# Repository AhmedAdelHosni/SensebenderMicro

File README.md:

# Sensebender Micro

UPDATE: The board was tested during month September 2017 and it works fine as a BETA testing.

This is a micro sensor module for Mysensors project: http://www.mysensors.org

Designed to run on 2 x AA(A) batteries, depending on how often one would
like to replace the batteries. 

This branch replaces the 0402 passive components to 0603 package size.

The sensor includes the following peripherals
- Jedec compatible eeprom/flash footprint
- ATSHA204A for authentication

This branch removed the following
- Si7021 Temperature / Humidity sensor (Connected to I2C bus)
- LED

The following pins are available on headers:

- Powersupply (1.8 -> 3.5V)
- SDA / SCL (I2C bus)
- A0 / A1
- D3 / D4 / D5 / D6 / D7
- 6 pin ISP port
- 8 pin standard NRF24L01+ connector layout
- FTDI header for serial

*Please note*

MAXIMUM allowed supply voltage is 3.5V, anything above this WILL fry both
radio and NRF24 radio module. There is NO voltage regulator on board (To keep
supply current down to a minimum)

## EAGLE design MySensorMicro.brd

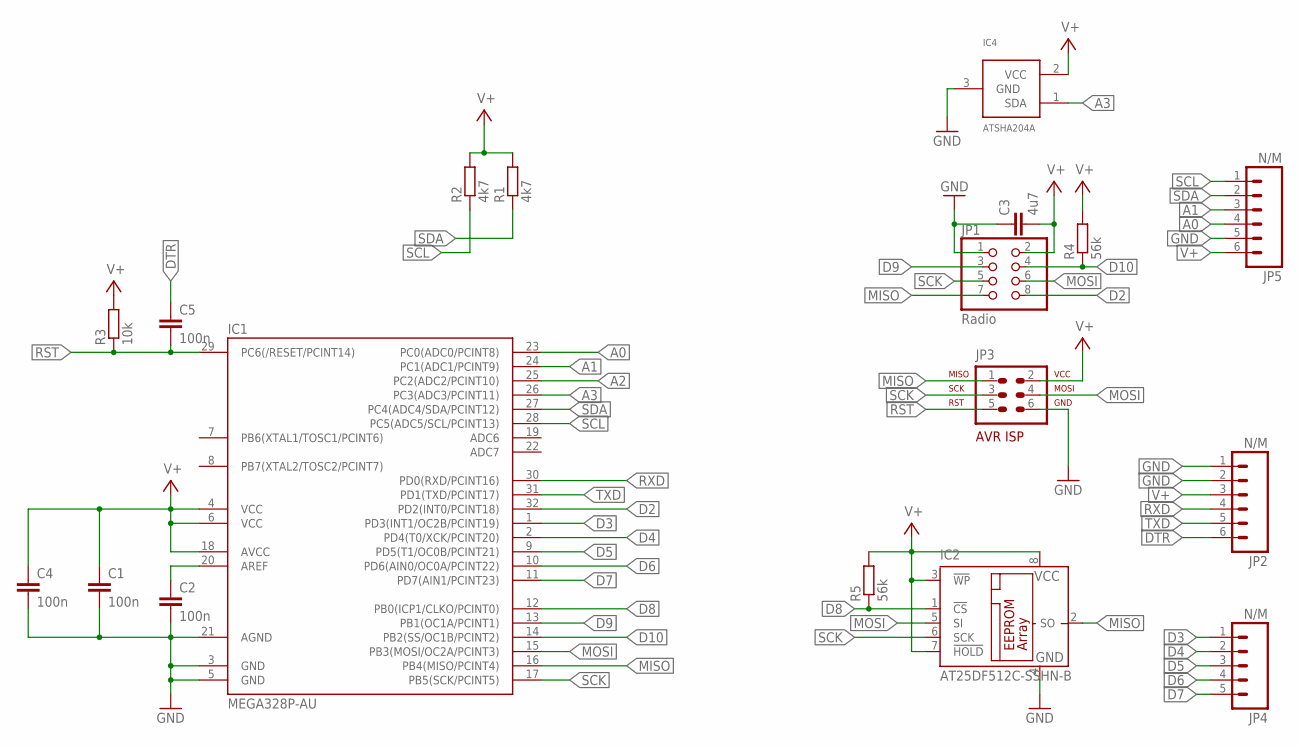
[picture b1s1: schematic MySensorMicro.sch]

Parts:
C1, C2, C4, C5: 100n; C0603K
C3: 4u7; C0603K
IC1: MEGA328P-AU; TQFP32-08
IC2: AT25DF512C-SSHN-B; SO-08
IC4: ATSHA204A; SOT23
JP1: Radio; 2X04
JP2, JP5: N/M; 1X06_NO_SILK
JP3: N/M; AVR-ISP-6
JP4: N/M; 1X05_NO_SILK
R1, R2: 4k7; R0603
R3: 10k; R0603
R4, R5: 56k; R0603

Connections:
A0: IC1.23 (PC0(ADC0/PCINT8)), JP5.4
A1: IC1.24 (PC1(ADC1/PCINT9)), JP5.3
A2: IC1.25 (PC2(ADC2/PCINT10))
A3: IC1.26 (PC3(ADC3/PCINT11)), IC4.1 (SDA)
D2: IC1.32 (PD2(INT0/PCINT18)), JP1.8
D3: IC1.1 (PD3(INT1/OC2B/PCINT19)), JP4.1
D4: IC1.2 (PD4(T0/XCK/PCINT20)), JP4.2
D5: IC1.9 (PD5(T1/OC0B/PCINT21)), JP4.3
D6: IC1.10 (PD6(AIN0/OC0A/PCINT22)), JP4.4
D7: IC1.11 (PD7(AIN1/PCINT23)), JP4.5
D8: IC1.12 (PB0(ICP1/CLKO/PCINT0)), IC2.1 (!CS), R5.1
D9: IC1.13 (PB1(OC1A/PCINT1)), JP1.3
D10: IC1.14 (PB2(SS/OC1B/PCINT2)), JP1.4, R4.1
DTR: C5.1, JP2.6
GND: C1.2, C2.2, C3.1, C4.2, IC1.3 (GND), IC1.5 (GND), IC1.21 (AGND), IC2.4 (GND), IC4.3 (GND), JP1.1, JP2.1, JP2.2, JP3.6, JP5.5
MISO: IC1.16 (PB4(MISO/PCINT4)), IC2.2 (SO), JP1.7, JP3.1
MOSI: IC1.15 (PB3(MOSI/OC2A/PCINT3)), IC2.5 (SI), JP1.6, JP3.4
unnamed: C2.1, IC1.20 (AREF)
RST: C5.2, IC1.29 (PC6(/RESET/PCINT14)), JP3.5, R3.1
RXD: IC1.30 (PD0(RXD/PCINT16)), JP2.4
SCK: IC1.17 (PB5(SCK/PCINT5)), IC2.6 (SCK), JP1.5, JP3.3
SCL: IC1.28 (PC5(ADC5/SCL/PCINT13)), JP5.1, R2.1
SDA: IC1.27 (PC4(ADC4/SDA/PCINT12)), JP5.2, R1.1
TXD: IC1.31 (PD1(TXD/PCINT17)), JP2.5
V+: C1.1, C3.2, C4.1, IC1.4 (VCC), IC1.6 (VCC), IC1.18 (AVCC), IC2.3 (!WP), IC2.7 (!HOLD), IC2.8 (VCC), IC4.2 (VCC), JP1.2, JP2.3, JP3.2, JP5.6, R1.2, R2.2, R3.2, R4.2, R5.2

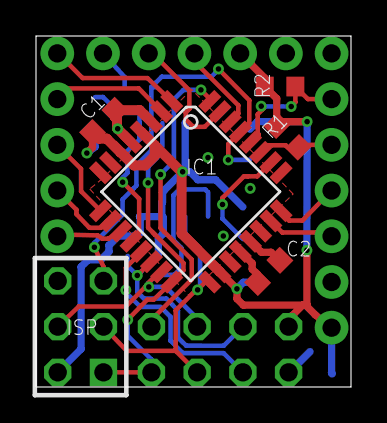
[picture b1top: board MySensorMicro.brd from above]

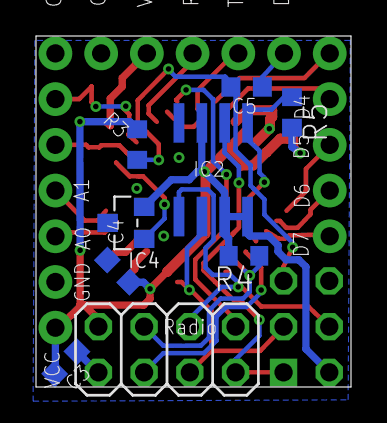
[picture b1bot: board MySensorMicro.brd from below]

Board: 2 copper layers, 17.5 x 19.5 mm, 18 parts (9 on the bottom side), 24 nets.

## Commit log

2016-03-14 Change passive components in schematic to 0603 package
    This initial branch includes changes in the following:
    - schematic layout: change passive components to 0603 package.
    - board layout: NOT yet in the correct position as the new package size
    caused overlaps with other components. This will be fixed in next
    releases.
2016-03-14 Update README.md
    This branch replaces the 0402 passive components to 0603 package size.
2016-03-18 Adapt PCB layout to 0603 package size "major change"
    * Schematic
    - rotate C5
    - delete X1 "crystal"
    * PCB Layout "major change"
    - Change board size to 19.5x17.5
    - All passive componets are changed to 0603 package size
2016-04-08 Change wire width of D9, D10 and MOSI
    Changed width to 10 mils
2017-09-28 Revert back readme info

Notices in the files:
parts and their libraries:
SparkFun-Connectors: Licensing: Creative Commons ShareAlike 4.0 International - https://creativecommons.org/licenses/by-sa/4.0
